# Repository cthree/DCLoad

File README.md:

DCLoad
======

A Simple DC Constant Current Load Project to build yourself. 

Minimum Specs:

- 20 Watt maximum load (thermal limitation)
- Adjustible current sink up to 30V (relay limitiation)
- Load switch and indicator
- 12 VDC fused power supply with switch and indicator
- Easily modified and expanded
- Modulated dynamic load with function generator (WIP)
- Most sections optional, many jellybean parts

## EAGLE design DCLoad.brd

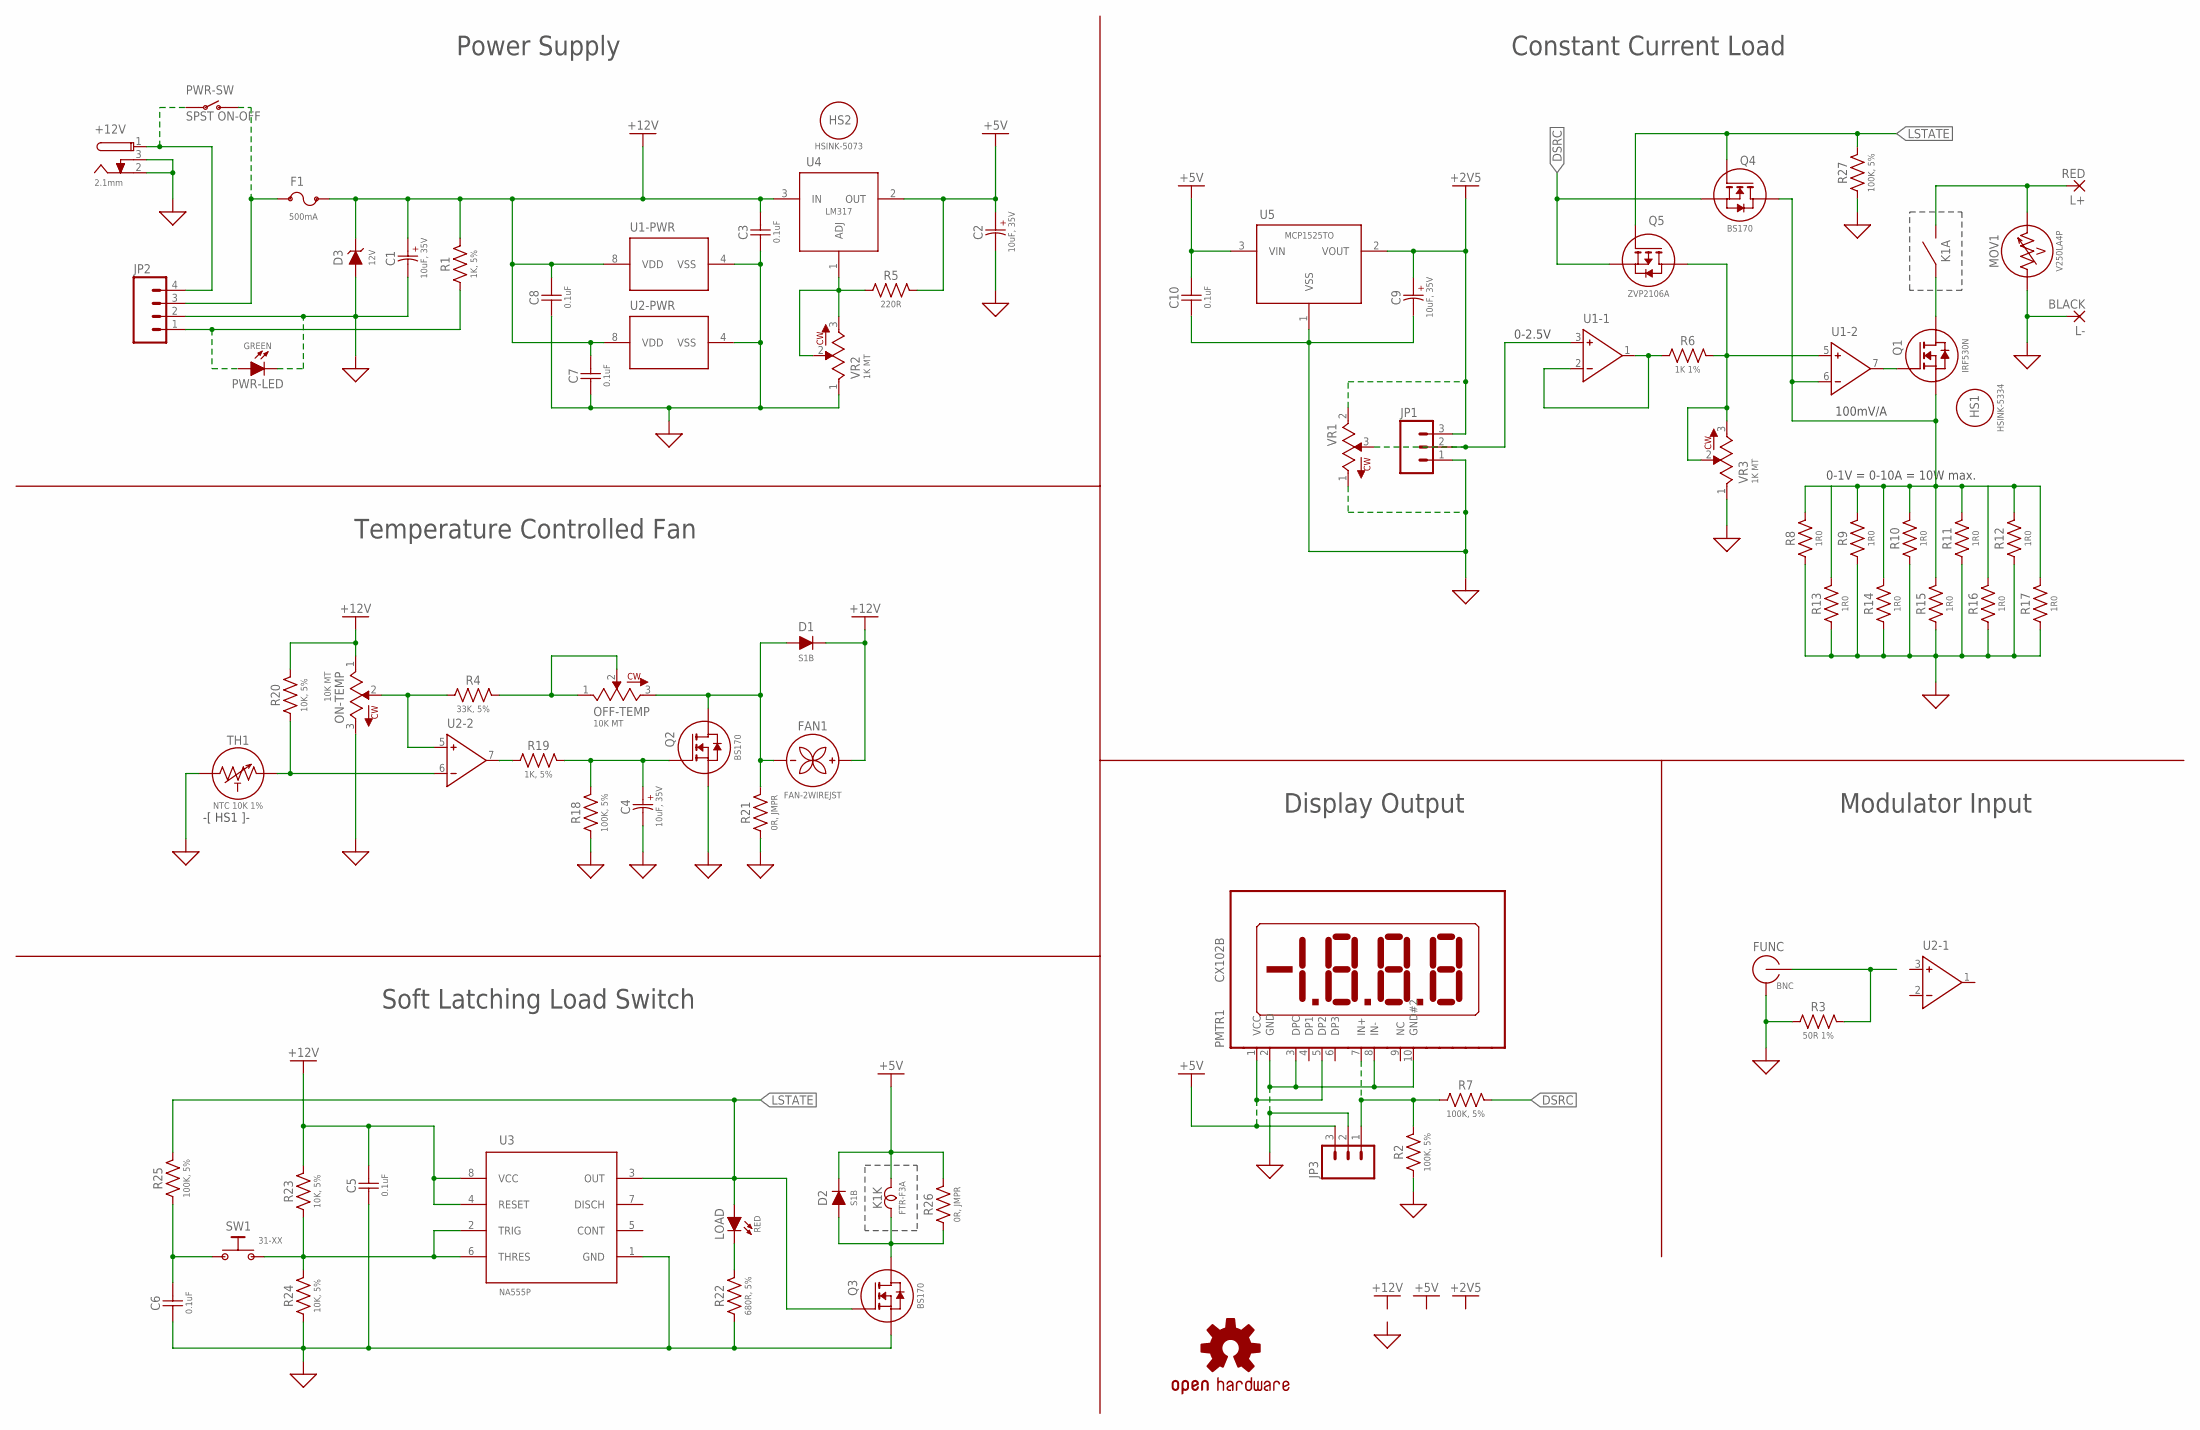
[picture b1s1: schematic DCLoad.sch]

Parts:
+12V: 2.1mm; PJ-102A
C1, C2, C4, C9: 10uF, 35V; 5RAL
C3, C5, C6, C7, C8, C10: 0.1uF; 18-0603
D1, D2: S1B; DO-214AC
D3: 12V; DO-214AC
F1: 500mA; 1206
FAN1: FAN-2WIREJST; JST-2-PTH
FUNC: BNC
HS1: HSINK-5334; 5334
HS2: HSINK-5073; 5073
JP1, JP3: M03POLAR; MOLEX-1X3
JP2: M04POLAR; MOLEX-1X4
K1: FTR-F3A; FTR-F3STD
L+: RED; 2,54/1,0
L-: BLACK; 2,54/1,0
LOAD: RED; LED5MM
LOGO1: OSHW-LOGOM; OSHW-LOGO-M
MOV1: V250LA4P; S07K17
OFF-TEMP: 10K MT; 3296W
ON-TEMP: 10K MT; 3296W
PMTR1: CX102B; CX102
PWR-LED: GREEN; LED5MM
PWR-SW: SPST ON-OFF; SWITCH-SPST-VERTICAL
Q1: IRF530N; TO220-3
Q2, Q3, Q4: BS170; TO-92
Q5: ZVP2106A; TO-92
R1, R19: 1K, 5%; R0603
R2, R7, R18, R25, R27: 100K, 5%; R0603
R3: 50R 1%; 0204/7
R4: 33K, 5%; R0603
R5: 220R; 0204/7
R6: 1K 1%; 0204/7
R8, R9, R10, R11, R12, R13, R14, R15, R16, R17: 1R0; 2512
R20, R23, R24: 10K, 5%; R0603
R21, R26: 0R, JMPR; R0603
R22: 680R, 5%; R0603
SW1: 31-XX; B3F-31XX
TH1: NTC 10K 1%; BEAD-THERM
U1, U2: TLC272ACP; PDIP-8
U3: NA555P; DIP254P762X508-8
U4: LM317; TO-220AB
U5: MCP1525TO; TO127P254X495-3
VR1: 10TPOT
VR2, VR3: 1K MT; 3296W

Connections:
+5V: C2.P, D2.C, JP3.3, K1.2, PMTR1.1 (VCC), PMTR1.5 (DP2), R5.2, R26.2, U4.2 (OUT)
+12V: C1.P, C3.2, C5.2, C7.2, C8.2, C10.2, D1.C, D3.C, F1.2, FAN1.2 (NEG(-)), ON-TEMP.1, R1.2, R20.2, R23.2, U1.8 (VDD), U2.8 (VDD), U3.4 (RESET), U3.8 (VCC), U4.3 (IN), U5.3 (VIN)
DSRC: Q4.3 (S), Q5.3 (S), R7.2
GND: +12V.2, +12V.3, C1.N, C2.N, C3.1, C4.N, C5.1, C6.1, C7.1, C8.1, C9.N, C10.1, D3.A, FUNC.GND, JP1.1, JP2.2, JP3.2, L-.1, MOV1.2, ON-TEMP.3, PMTR1.2 (GND), PMTR1.3 (DPC), PMTR1.8 (IN-), PMTR1.10 (GND#2), PWR-LED.K (C), Q2.3 (S), Q3.3 (S), R2.1, R3.1, R8.1, R9.1, R10.1, R11.1, R12.1, R13.1, R14.1, R15.1, R16.1, R17.1, R18.1, R21.1, R22.1, R24.1, R27.1, SW1.GND@1 (GND), SW1.GND@2 (GND), TH1.P$1 (1), U1.4 (VSS), U2.4 (VSS), U3.1 (GND), U5.1 (VSS), VR1.1 (3), VR2.1, VR3.1
LSTATE: LOAD.A, Q3.2 (G), Q4.2 (G), Q5.2 (G), R25.2, R27.2, U3.3 (OUT)
unnamed: FUNC.S (OUT), R3.2
unnamed: +12V.1, JP2.4, PWR-SW.2
unnamed: Q1.1 (G), U1.7 (OUT)
unnamed: R5.1, U4.1 (ADJ), VR2.2, VR2.3
unnamed: K1.4 (2), L+.1, MOV1.1
unnamed: D1.A, FAN1.1 (POS(+)), OFF-TEMP.3, Q2.1 (D), R21.2
unnamed: R20.1, TH1.P$2 (2), U2.6 (IN-)
unnamed: ON-TEMP.2, R4.1, U2.5 (IN+)
unnamed: R19.1, U2.7 (OUT)
unnamed: D2.A, K1.1, Q3.1 (D), R26.1
unnamed: C4.P, Q2.2 (G), R18.2, R19.2
unnamed: OFF-TEMP.1, OFF-TEMP.2, R4.2
unnamed: C6.2, R25.1, SW1.1
unnamed: R6.1, U1.1 (OUT), U1.2 (IN-)
unnamed: LOAD.K (C), R22.2
unnamed: R23.1, R24.2, SW1.2, U3.2 (TRIG), U3.6 (THRES)
unnamed: F1.1, JP2.3, PWR-SW.1 (O)
unnamed: JP1.2, U1.3 (IN+), VR1.3 (2)
unnamed: K1.3 (1), Q1.2 (D)
unnamed: JP3.1, PMTR1.7 (IN+), R2.2, R7.1
unnamed: JP2.1, PWR-LED.A, R1.1
SENSE: Q1.3 (S), Q4.1 (D), R8.2, R9.2, R10.2, R11.2, R12.2, R13.2, R14.2, R15.2, R16.2, R17.2, U1.6 (IN-)
SET: Q5.1 (D), R6.2, U1.5 (IN+), VR3.2, VR3.3
VREF: C9.P, JP1.3, U5.2 (VOUT), VR1.2 (1)

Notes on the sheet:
-[ HS1 ]-
Constant Current Load
Power Supply
Temperature Controlled Fan
Soft Latching Load Switch
0-2.5V
100mV/A
0-1V = 0-10A = 10W max.
Modulator Input
Display Output

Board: 2 copper layers, 75 parts (0 on the bottom side), 29 nets, no tracks yet.

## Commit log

2014-03-24 Added PDF Schematic

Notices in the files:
parts and their libraries:
SparkFun-Connectors: Licensing: CC v3.0 Share-Alike You are welcome to use this library for commercial purposes.
